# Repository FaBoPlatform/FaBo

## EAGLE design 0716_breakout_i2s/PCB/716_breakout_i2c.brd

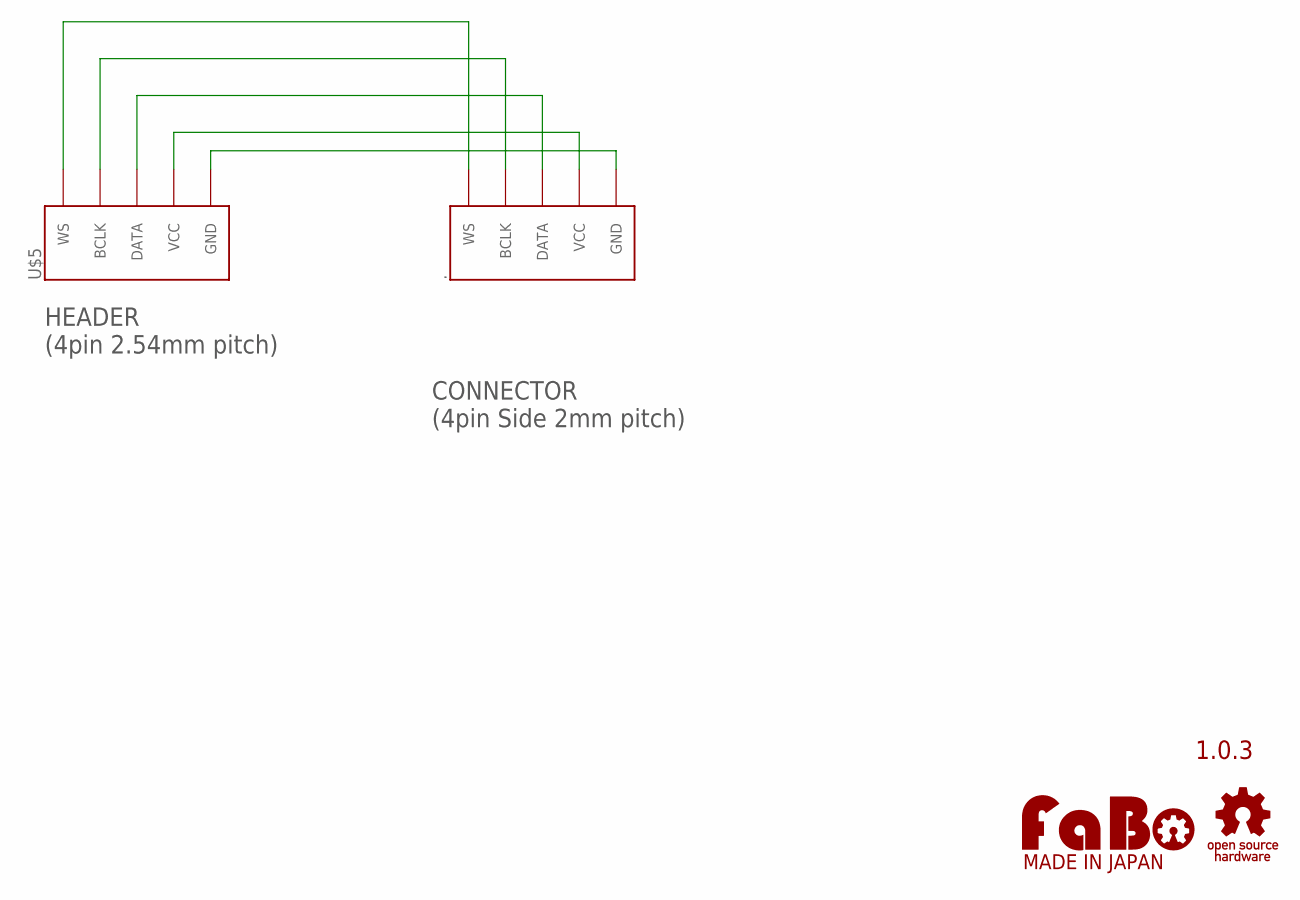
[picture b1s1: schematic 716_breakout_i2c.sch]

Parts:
.: FABO_BRICK_I2SLONG; FABO_BRICK_I2S_S05B-PASK-2_LONG
U$2: LOGO_FABO-M_BOTTOM; LOGO_FABO_MS_BOTTOM
U$3: LOGO_OSHW-S_BOTTOM; LOGO_OSHW_S_BOTTOM
U$5: FABO_BRICK_I2S-BREAKOUT; FABO_BRICK_I2S_BREAKOUT

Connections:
BCLK: ..BCLK, U$5.BCLK
DATA: ..DATA, U$5.DATA
GND: ..GND, U$5.GND
VCC: ..VCC, U$5.VCC
WS: ..WS, U$5.WS

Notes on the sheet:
1.0.3
CONNECTOR (4pin Side 2mm pitch)
HEADER (4pin 2.54mm pitch)

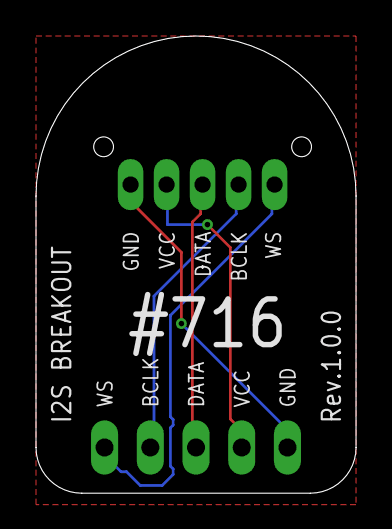
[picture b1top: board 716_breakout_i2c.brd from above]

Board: 2 copper layers, 17.8 x 25.4 mm, 4 parts (0 on the bottom side), 5 nets.

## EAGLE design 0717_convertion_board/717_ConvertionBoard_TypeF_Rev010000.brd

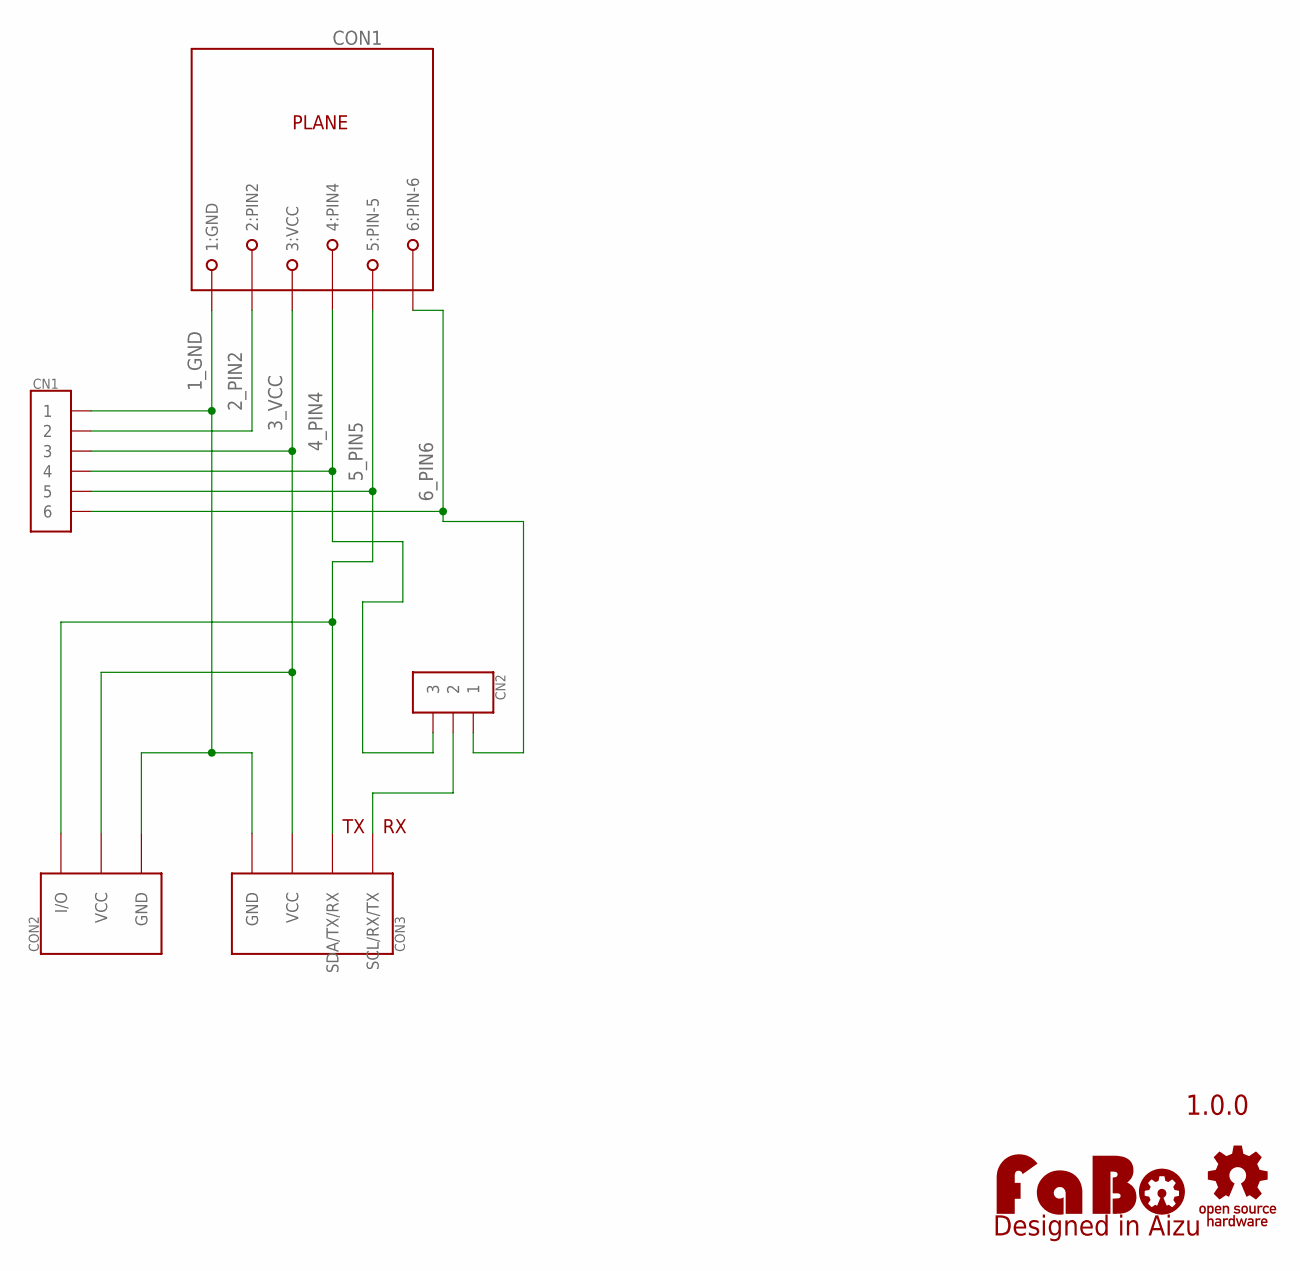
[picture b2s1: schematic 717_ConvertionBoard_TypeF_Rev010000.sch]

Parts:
CN1: PIN_1X6
CN2: PIN_1X3
CON1: MODULAR-JACK-6P-PLANE; 7002-6PXC-X
CON2: FABO_BRICK_3PIN-S03B-PASK-2; FABO_BRICK_3PIN_S03B-PASK-2
CON3: FABO_BRICK_4PIN; FABO_BRICK_PLANE_S04B-PASK-2
LOGO1: LOGO_FABO-M; LOGO_FABO_M
U$2: LOGO_OSHW-M_BOTTOM; LOGO_OSHW_M_BOTTOM

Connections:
1_GND: CN1.1, CON1.1 (1:GND), CON2.GND, CON3.GND
2_PIN2: CN1.2, CON1.2 (2:PIN2)
3_VCC: CN1.3, CON1.3 (3:VCC), CON2.VCC, CON3.VCC
4_PIN4: CN1.4, CN2.3, CON1.4 (4:PIN4)
5_PIN5: CN1.5, CON1.5 (5:PIN-5), CON2.I/O, CON3.3 (SDA/TX/RX)
6_PIN6: CN1.6, CN2.1, CON1.6 (6:PIN-6)
RX: CN2.2, CON3.4 (SCL/RX/TX)

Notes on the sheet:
1.0.0

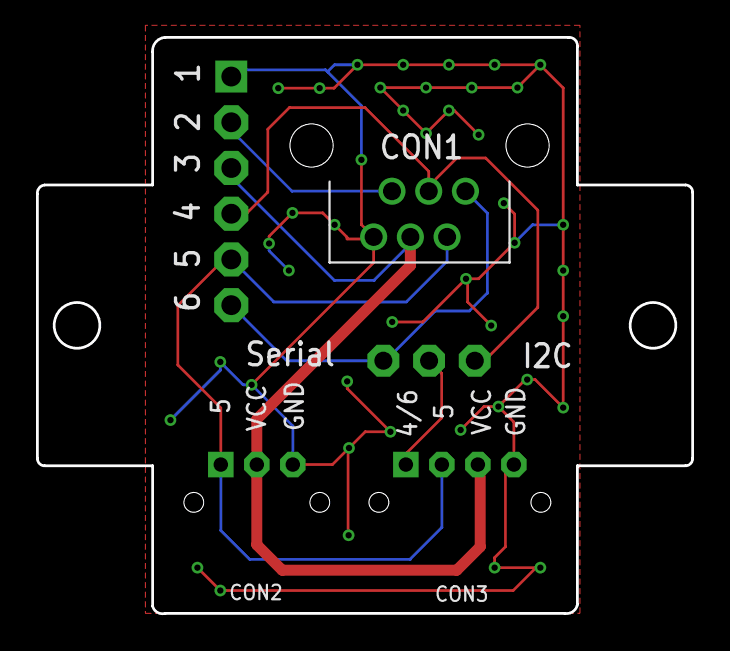
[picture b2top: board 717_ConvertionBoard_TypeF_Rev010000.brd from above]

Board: 2 copper layers, 36.4 x 32.0 mm, 9 parts (1 on the bottom side), 7 nets.

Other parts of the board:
U$3, U$4: 4-1BLOCK

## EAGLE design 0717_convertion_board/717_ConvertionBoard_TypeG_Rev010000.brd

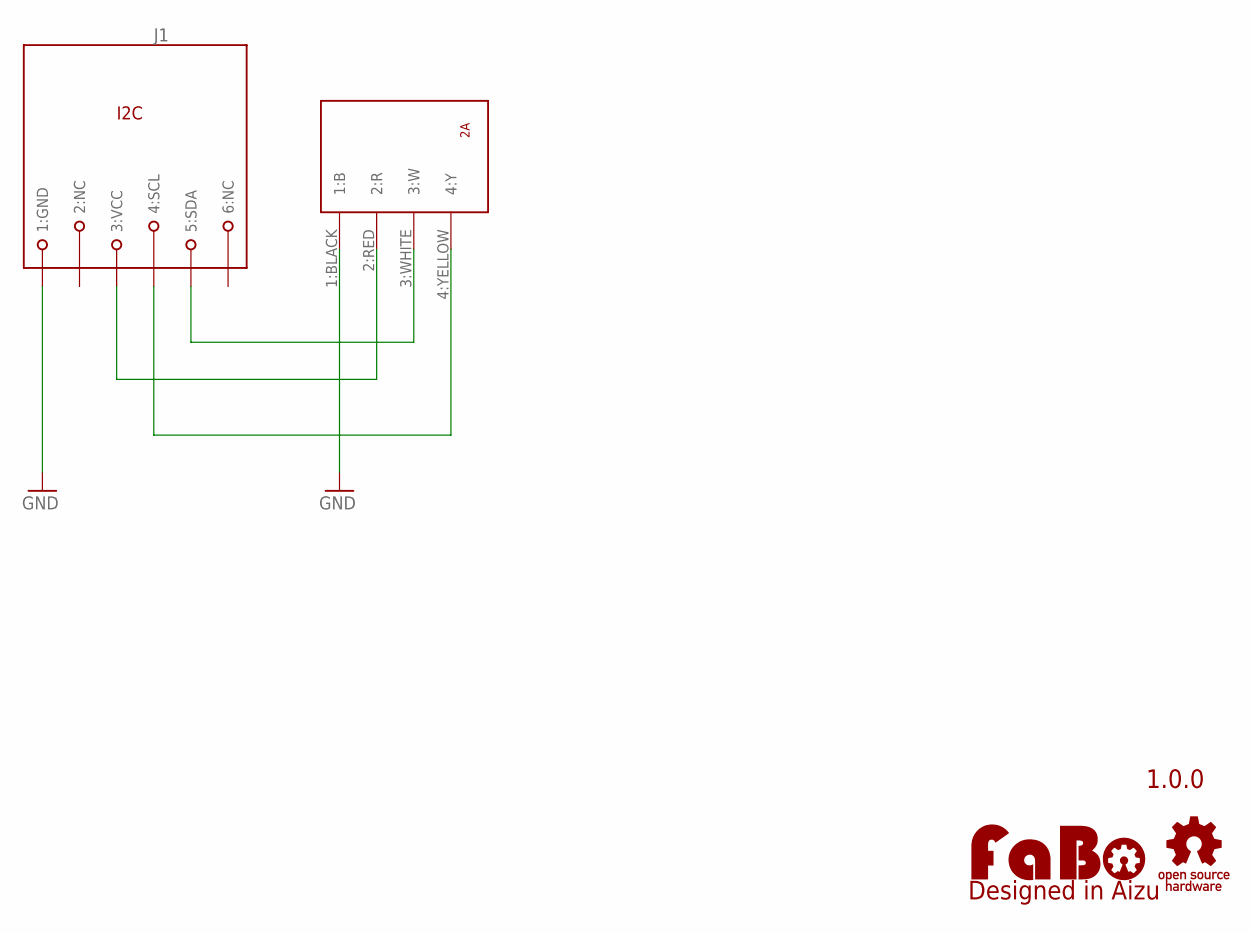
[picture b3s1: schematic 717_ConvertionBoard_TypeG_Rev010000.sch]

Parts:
J1: MODULAR-JACK-6P-RJ11_I2C; 7002-6PXC-X
LOGO1: LOGO_FABO-M; LOGO_FABO_M
U$2: LOGO_OSHW-M_BOTTOM; LOGO_OSHW_M_BOTTOM
U$6: SG_PIN_4_SMD_SIDE; 114020164

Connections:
GND: J1.1 (1:GND), U$6.1:BLACK (1:B)
unnamed: J1.3 (3:VCC), U$6.2:RED (2:R)
unnamed: J1.4 (4:SCL), U$6.4:YELLOW (4:Y)
unnamed: J1.5 (5:SDA), U$6.3:WHITE (3:W)

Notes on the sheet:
1.0.0

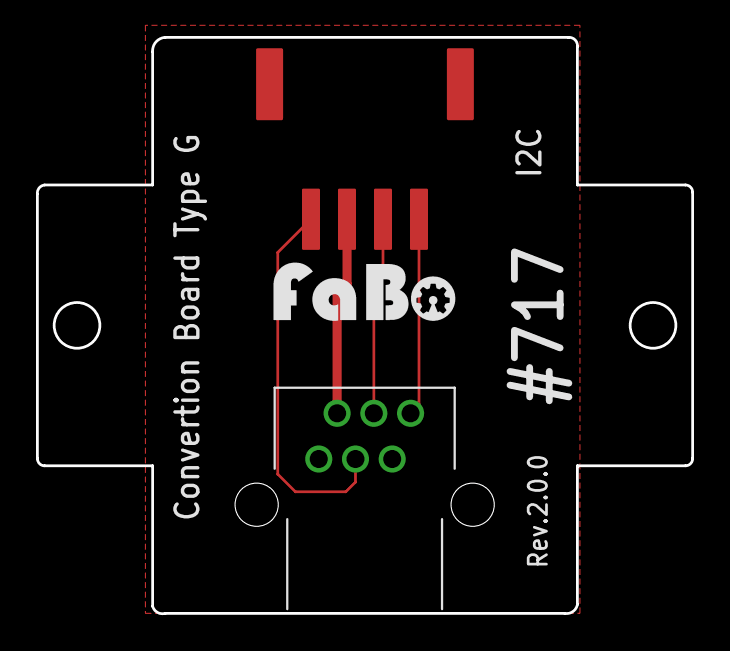
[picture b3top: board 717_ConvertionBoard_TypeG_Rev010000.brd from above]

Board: 2 copper layers, 36.4 x 32.0 mm, 6 parts (0 on the bottom side), 4 nets.

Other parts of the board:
U$3, U$4: 4-1BLOCK

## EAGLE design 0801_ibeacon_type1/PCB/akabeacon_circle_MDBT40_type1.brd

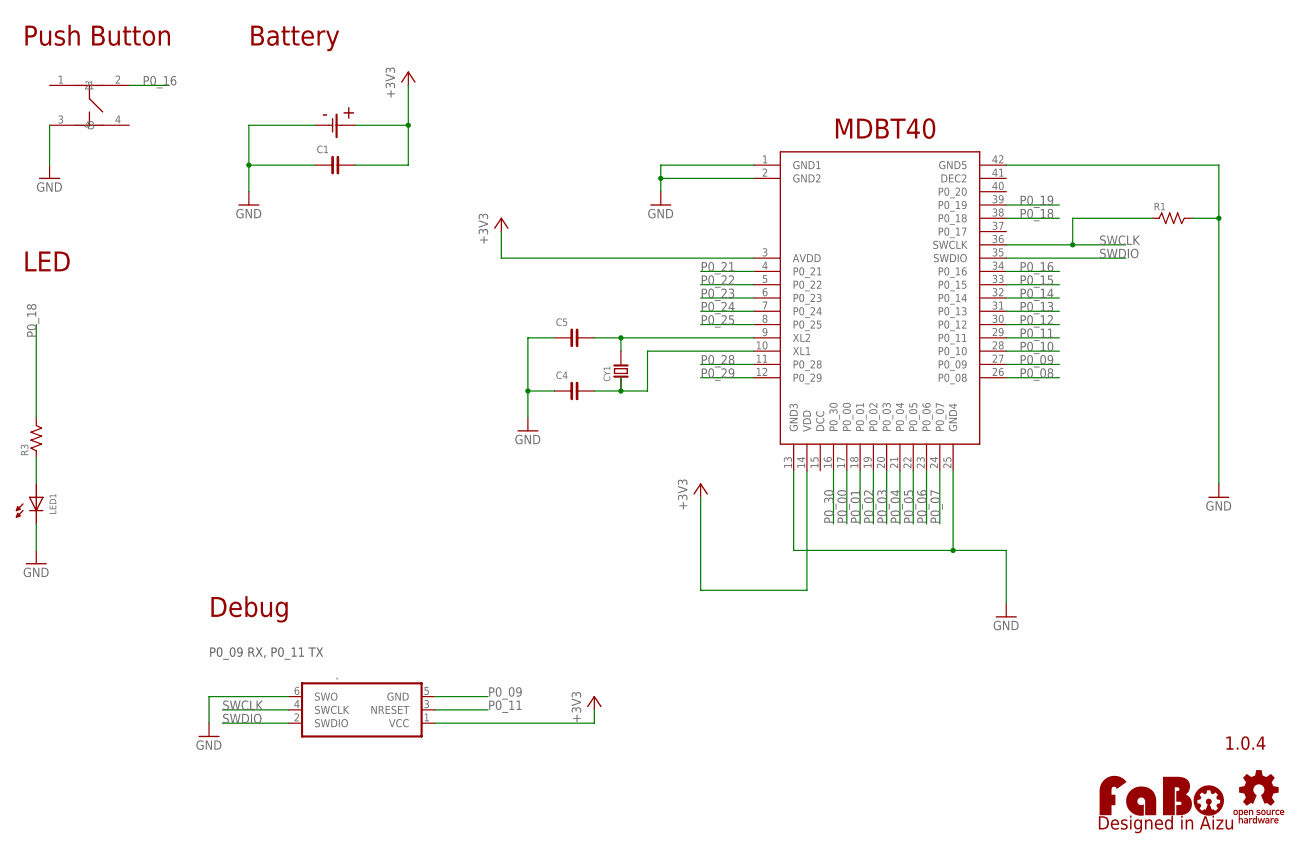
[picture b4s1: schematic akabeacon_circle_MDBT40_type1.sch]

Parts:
.: TC2030-IDC-NL
C1, C4, C5: CAPACITOR-0603; 0603
CY1: CRYSTALABS07; ABRACON-ABS07-32.768KHZ
LED1: LED-0603; 0603
R1, R3: RESISTOR-0603; 0603
U$1: RAYTAC-MDBT40
U$2: CH031-2477LF
U$3: LOGO_FABO-M; LOGO_FABO_MS
U$4: LOGO_OSHW-M_BOTTOM; LOGO_OSHW_M_BOTTOM
U$5: SWICTH-4P(KMR2); SWITCH-4P(KMR2)

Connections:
+3V3: ..1 (VCC), C1.2, U$1.3 (AVDD), U$1.14 (VDD), U$2.+
GND: ..6 (SWO), C1.1, C4.1, C5.1, LED1.CATHODE, R1.2, U$1.1 (GND1), U$1.2 (GND2), U$1.13 (GND3), U$1.25 (GND4), U$1.42 (GND5), U$2.-, U$5.3
unnamed: LED1.ANODE, R3.1
unnamed: C5.2, CY1.P$2, U$1.9 (XL2)
unnamed: C4.2, CY1.P$1, U$1.10 (XL1)
P0_00: U$1.17 (P0_00)
P0_01: U$1.18 (P0_01)
P0_02: U$1.19 (P0_02)
P0_03: U$1.20 (P0_03)
P0_04: U$1.21 (P0_04)
P0_05: U$1.22 (P0_05)
P0_06: U$1.23 (P0_06)
P0_07: U$1.24 (P0_07)
P0_08: U$1.26 (P0_08)
P0_09: ..5 (GND), U$1.27 (P0_09)
P0_10: U$1.28 (P0_10)
P0_11: ..3 (NRESET), U$1.29 (P0_11)
P0_12: U$1.30 (P0_12)
P0_13: U$1.31 (P0_13)
P0_14: U$1.32 (P0_14)
P0_15: U$1.33 (P0_15)
P0_16: U$1.34 (P0_16), U$5.2
P0_18: R3.2, U$1.38 (P0_18)
P0_19: U$1.39 (P0_19)
P0_21: U$1.4 (P0_21)
P0_22: U$1.5 (P0_22)
P0_23: U$1.6 (P0_23)
P0_24: U$1.7 (P0_24)
P0_25: U$1.8 (P0_25)
P0_28: U$1.11 (P0_28)
P0_29: U$1.12 (P0_29)
P0_30: U$1.16 (P0_30)
SWCLK: ..4 (SWCLK), R1.1, U$1.36 (SWCLK)
SWDIO: ..2 (SWDIO), U$1.35 (SWDIO)

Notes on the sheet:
Battery
Push Button
MDBT40
LED
Debug
P0_09 RX, P0_11 TX
1.0.4

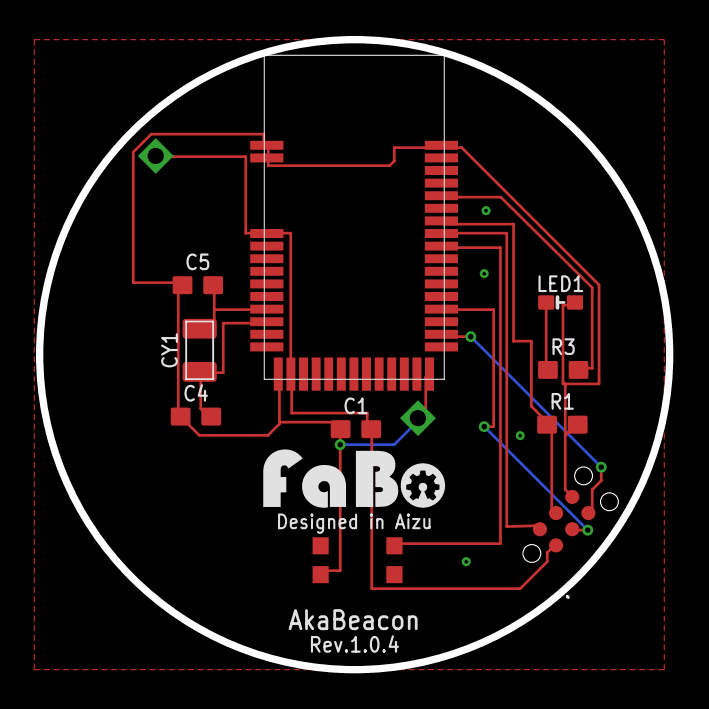
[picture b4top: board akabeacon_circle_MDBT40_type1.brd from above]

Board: 2 copper layers, 35.0 x 35.0 mm, 13 parts (0 on the bottom side), 11 nets.

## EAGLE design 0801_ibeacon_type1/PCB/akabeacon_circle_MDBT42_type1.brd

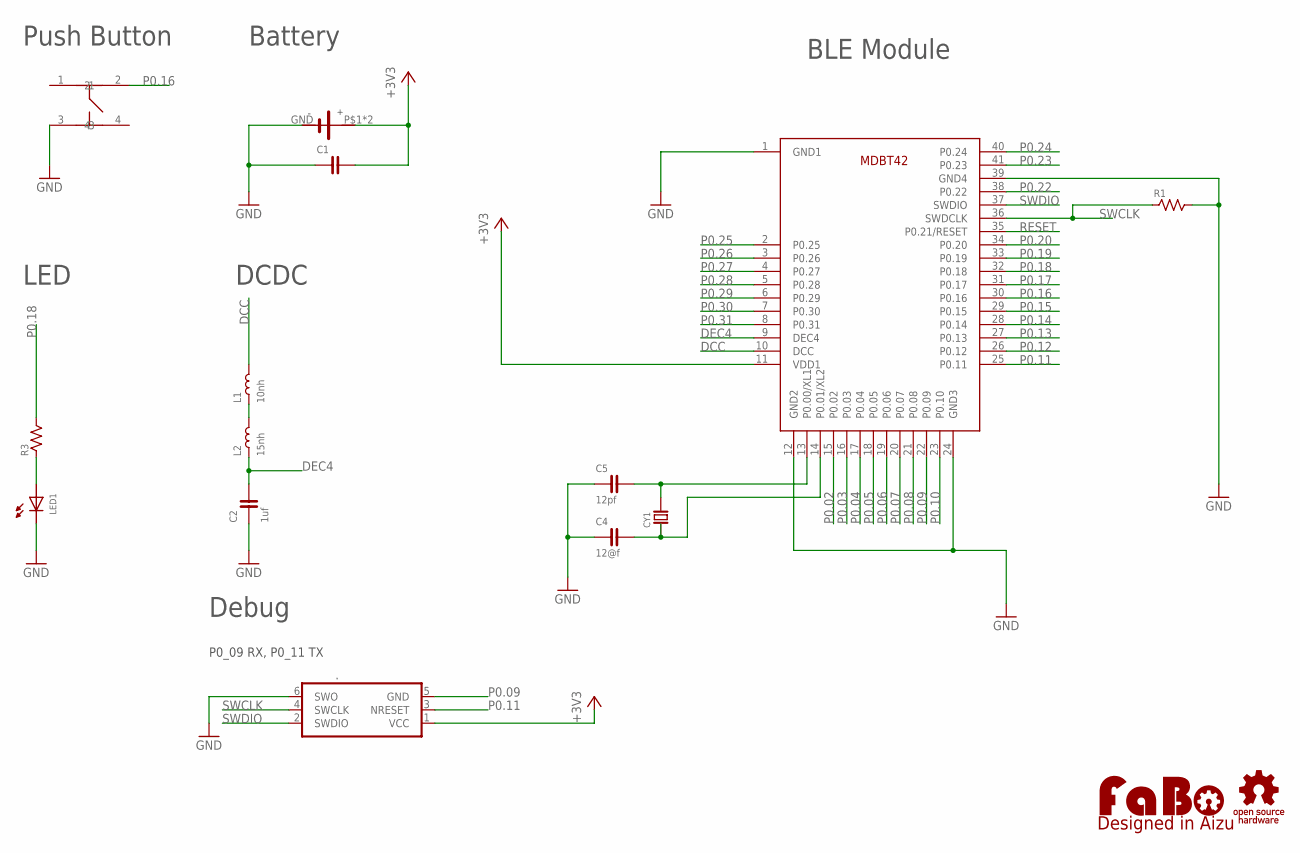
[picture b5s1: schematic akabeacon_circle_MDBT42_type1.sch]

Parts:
.: TC2030-IDC-NL
C1: CAPACITOR-0603; 0603
C2: 1uf; 0603
C4: 12@f; 0603
C5: 12pf; 0603
CY1: CRYSTAL-ABS07; ABRACON-ABS07-32.768KHZ
L1: 10nh; 0603
L2: 15nh; 0603
LED1: LED-0603; 0603
R1, R3: RESISTOR-0603; 0603
U$1: LOGO_OSHW-M_BOTTOM; LOGO_OSHW_M_BOTTOM
U$2: RAYTAC-MDBT42
U$3: CIRCLE-TYPE2; CIRCLE-TYPE2-TC2030
U$4: LOGO_FABO-M_BOTTOM; LOGO_FABO_MS_BOTTOM
U$5: SWICTH-4P(KMR2); SWITCH-4P(KMR2)

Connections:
+3V3: ..1 (VCC), C1.2, U$2.11 (VDD1), U$3.P$1 (VCC), U$3.P$2 (VCC)
DCC: L1.2, U$2.10 (DCC)
DEC4: C2.2, L2.1, U$2.9 (DEC4)
GND: ..6 (SWO), C1.1, C2.1, C4.1, C5.1, LED1.CATHODE, R1.2, U$2.1 (GND1), U$2.12 (GND2), U$2.24 (GND3), U$2.39 (GND4), U$3.GND, U$5.3
unnamed: LED1.ANODE, R3.1
unnamed: L1.1, L2.2
unnamed: C5.2, CY1.P$2, U$2.13 (P0.00/XL1)
unnamed: C4.2, CY1.P$1, U$2.14 (P0.01/XL2)
P0.02: U$2.15 (P0.02)
P0.03: U$2.16 (P0.03)
P0.04: U$2.17 (P0.04)
P0.05: U$2.18 (P0.05)
P0.06: U$2.19 (P0.06)
P0.07: U$2.20 (P0.07)
P0.08: U$2.21 (P0.08)
P0.09: ..5 (GND), U$2.22 (P0.09)
P0.10: U$2.23 (P0.10)
P0.11: ..3 (NRESET), U$2.25 (P0.11)
P0.12: U$2.26 (P0.12)
P0.13: U$2.27 (P0.13)
P0.14: U$2.28 (P0.14)
P0.15: U$2.29 (P0.15)
P0.16: U$2.30 (P0.16), U$5.2
P0.17: U$2.31 (P0.17)
P0.18: R3.2, U$2.32 (P0.18)
P0.19: U$2.33 (P0.19)
P0.20: U$2.34 (P0.20)
P0.22: U$2.38 (P0.22)
P0.23: U$2.41 (P0.23)
P0.24: U$2.40 (P0.24)
P0.25: U$2.2 (P0.25)
P0.26: U$2.3 (P0.26)
P0.27: U$2.4 (P0.27)
P0.28: U$2.5 (P0.28)
P0.29: U$2.6 (P0.29)
P0.30: U$2.7 (P0.30)
P0.31: U$2.8 (P0.31)
RESET: U$2.35 (P0.21/RESET)
SWCLK: ..4 (SWCLK), R1.1, U$2.36 (SWDCLK)
SWDIO: ..2 (SWDIO), U$2.37 (SWDIO)

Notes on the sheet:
Battery
Push Button
BLE Module
LED
Debug
P0_09 RX, P0_11 TX
DCDC

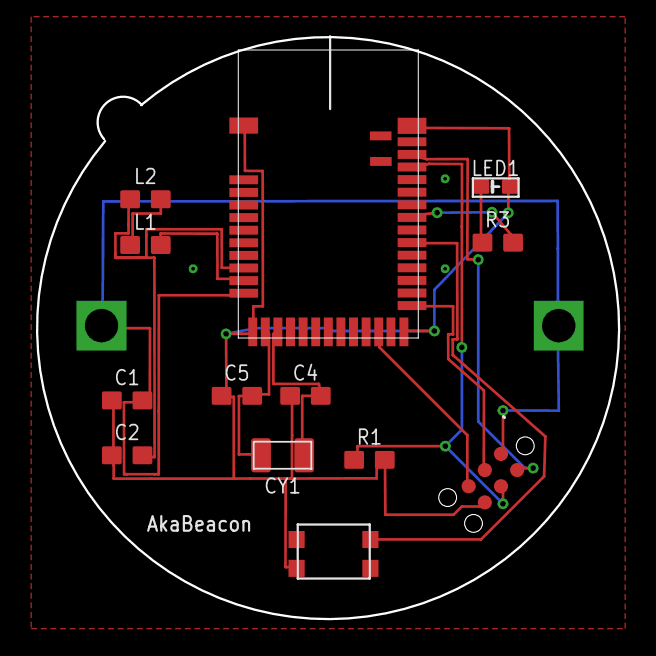
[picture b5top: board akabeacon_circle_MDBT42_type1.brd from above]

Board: 2 copper layers, 32.3 x 32.3 mm, 16 parts (0 on the bottom side), 14 nets.

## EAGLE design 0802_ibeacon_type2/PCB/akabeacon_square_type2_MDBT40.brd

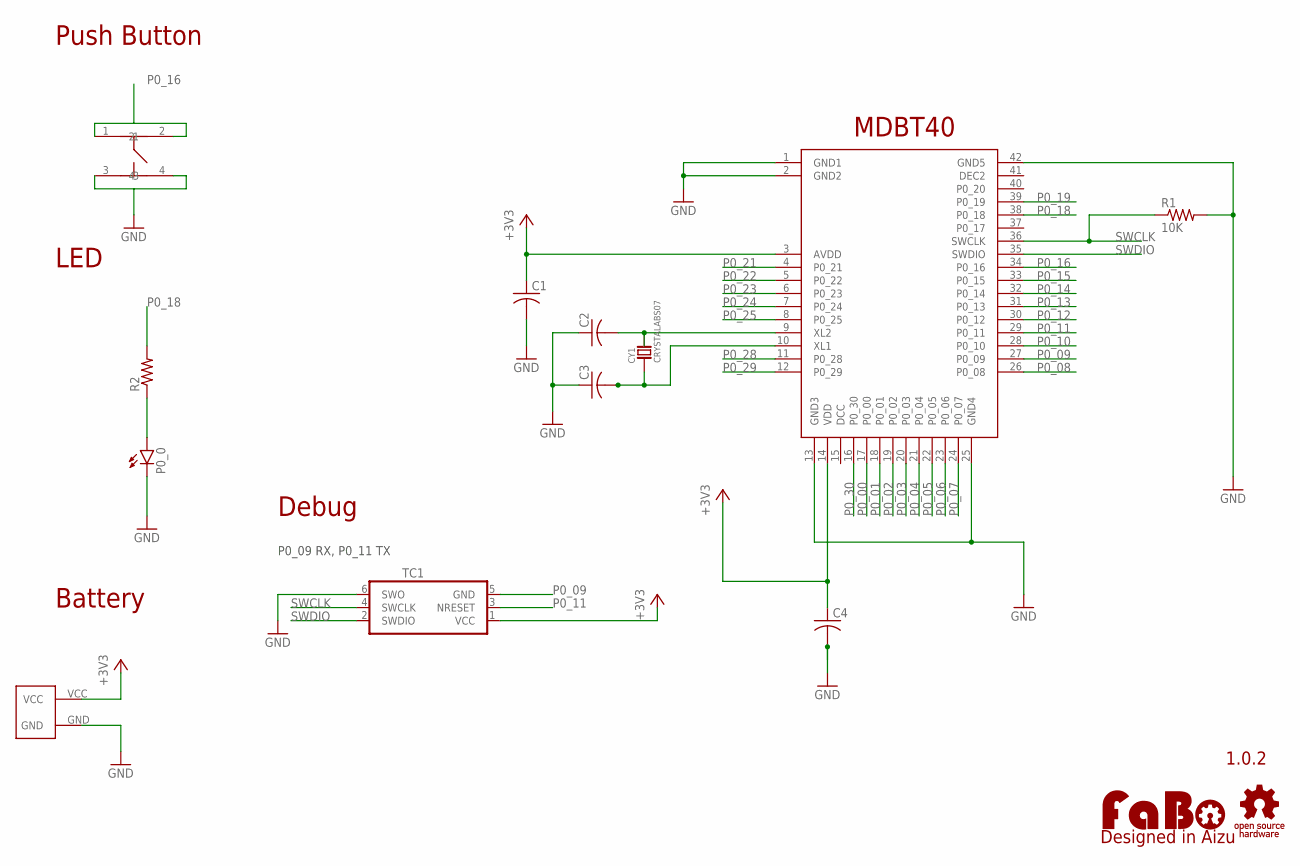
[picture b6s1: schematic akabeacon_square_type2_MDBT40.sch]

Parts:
C1, C2, C3, C4: C-USC0603; C0603
CY1: CRYSTALABS07; ABRACOM-ABS07-32.768KHZ
P0_0: LEDCHIP-LED0603; CHIP-LED0603
R1: 10K; R0603
R2: R-US_R0603; R0603
TC1: TC2030-IDC-NL
U$2: SQUARE-TYPE2-TC2030
U$3: RAYTAC-MDBT40
U$4: LOGO_OSHW-M; LOGO_OSHW_M
U$5: LOGO_FABO-M; LOGO_FABO_MS
U$6: SWICTH-4P(KMR2); SWITCH-4P(KMR2)

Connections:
+3V3: C1.1, C4.1, TC1.1 (VCC), U$2.VCC, U$3.3 (AVDD), U$3.14 (VDD)
GND: C1.2, C2.1, C3.1, C4.2, P0_0.C, R1.2, TC1.6 (SWO), U$2.GND, U$3.1 (GND1), U$3.2 (GND2), U$3.13 (GND3), U$3.25 (GND4), U$3.42 (GND5), U$6.3, U$6.4
unnamed: P0_0.A, R2.1
unnamed: C2.2, CY1.P$2, U$3.9 (XL2)
unnamed: C3.2, CY1.P$1, U$3.10 (XL1)
P0_00: U$3.17 (P0_00)
P0_01: U$3.18 (P0_01)
P0_02: U$3.19 (P0_02)
P0_03: U$3.20 (P0_03)
P0_04: U$3.21 (P0_04)
P0_05: U$3.22 (P0_05)
P0_06: U$3.23 (P0_06)
P0_07: U$3.24 (P0_07)
P0_08: U$3.26 (P0_08)
P0_09: TC1.5 (GND), U$3.27 (P0_09)
P0_10: U$3.28 (P0_10)
P0_11: TC1.3 (NRESET), U$3.29 (P0_11)
P0_12: U$3.30 (P0_12)
P0_13: U$3.31 (P0_13)
P0_14: U$3.32 (P0_14)
P0_15: U$3.33 (P0_15)
P0_16: U$3.34 (P0_16), U$6.1, U$6.2
P0_18: R2.2, U$3.38 (P0_18)
P0_19: U$3.39 (P0_19)
P0_21: U$3.4 (P0_21)
P0_22: U$3.5 (P0_22)
P0_23: U$3.6 (P0_23)
P0_24: U$3.7 (P0_24)
P0_25: U$3.8 (P0_25)
P0_28: U$3.11 (P0_28)
P0_29: U$3.12 (P0_29)
P0_30: U$3.16 (P0_30)
SWCLK: R1.1, TC1.4 (SWCLK), U$3.36 (SWCLK)
SWDIO: TC1.2 (SWDIO), U$3.35 (SWDIO)

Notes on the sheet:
Battery
Push Button
Debug
MDBT40
LED
P0_09 RX, P0_11 TX
1.0.2

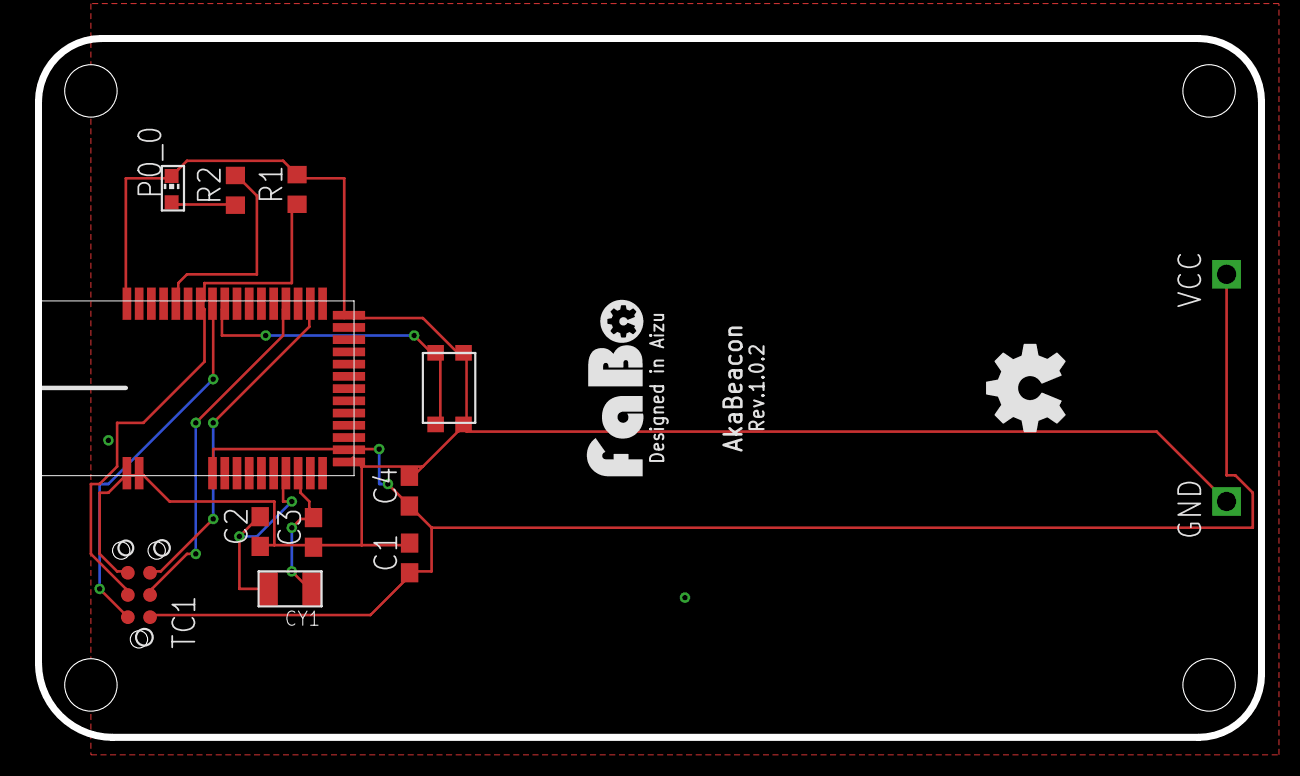
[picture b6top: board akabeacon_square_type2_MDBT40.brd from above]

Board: 2 copper layers, 70.0 x 40.0 mm, 14 parts (0 on the bottom side), 11 nets.

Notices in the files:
parts and their libraries:
FaBo-etc: Released under the Creative Commons Attribution-ShareAlike 4.0 License
https://creativecommons.org/licenses/by-sa/4.0
FaBo-etc: Released under the Creative Commons
SparkFun: Licensing: CC v3.0 Share-Alike You are welcome to use this library for commercial purposes.
